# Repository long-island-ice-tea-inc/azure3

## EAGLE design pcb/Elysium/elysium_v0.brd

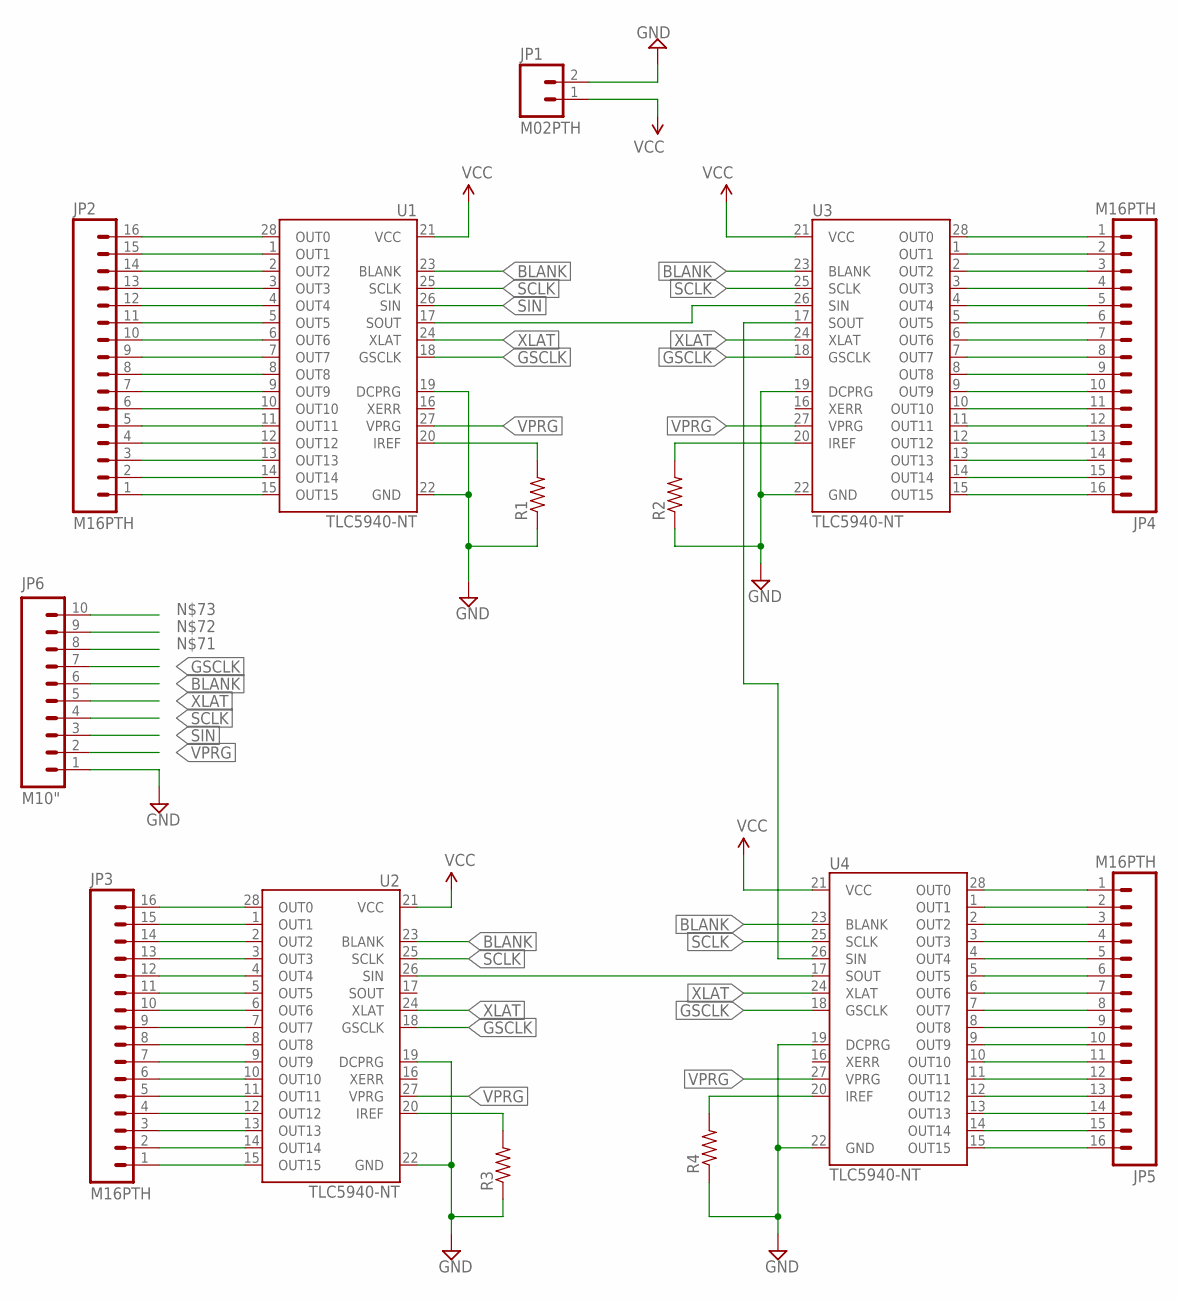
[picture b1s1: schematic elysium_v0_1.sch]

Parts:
JP1: M02PTH; 1X02
JP2, JP3, JP4, JP5: M16PTH; 1X16
JP6: M10"; 1X10
R1, R2, R3, R4: RESISTOREZ; AXIAL-0.3EZ
U1, U2, U3, U4: TLC5940-NT; DIL28-3

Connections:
BLANK: JP6.6, U1.23 (BLANK), U2.23 (BLANK), U3.23 (BLANK), U4.23 (BLANK)
GND: JP1.2, JP6.1, R1.P$1 (1), R2.P$1 (1), R3.P$1 (1), R4.P$1 (1), U1.19 (DCPRG), U1.22 (GND), U2.19 (DCPRG), U2.22 (GND), U3.19 (DCPRG), U3.22 (GND), U4.19 (DCPRG), U4.22 (GND)
GSCLK: JP6.7, U1.18 (GSCLK), U2.18 (GSCLK), U3.18 (GSCLK), U4.18 (GSCLK)
unnamed: JP2.16, U1.28 (OUT0)
unnamed: JP2.15, U1.1 (OUT1)
unnamed: JP2.14, U1.2 (OUT2)
unnamed: JP2.13, U1.3 (OUT3)
unnamed: JP2.12, U1.4 (OUT4)
unnamed: JP2.11, U1.5 (OUT5)
unnamed: JP2.10, U1.6 (OUT6)
unnamed: JP2.9, U1.7 (OUT7)
unnamed: JP2.8, U1.8 (OUT8)
unnamed: JP2.7, U1.9 (OUT9)
unnamed: JP2.6, U1.10 (OUT10)
unnamed: JP2.5, U1.11 (OUT11)
unnamed: JP2.4, U1.12 (OUT12)
unnamed: JP2.3, U1.13 (OUT13)
unnamed: JP2.2, U1.14 (OUT14)
unnamed: JP2.1, U1.15 (OUT15)
unnamed: JP4.1, U3.28 (OUT0)
unnamed: JP4.2, U3.1 (OUT1)
unnamed: JP4.3, U3.2 (OUT2)
unnamed: JP4.4, U3.3 (OUT3)
unnamed: JP4.5, U3.4 (OUT4)
unnamed: JP4.6, U3.5 (OUT5)
unnamed: JP4.7, U3.6 (OUT6)
unnamed: JP4.8, U3.7 (OUT7)
unnamed: JP4.9, U3.8 (OUT8)
unnamed: JP4.10, U3.9 (OUT9)
unnamed: JP4.11, U3.10 (OUT10)
unnamed: JP4.12, U3.11 (OUT11)
unnamed: JP4.13, U3.12 (OUT12)
unnamed: JP4.14, U3.13 (OUT13)
unnamed: JP4.15, U3.14 (OUT14)
unnamed: JP4.16, U3.15 (OUT15)
unnamed: JP3.16, U2.28 (OUT0)
unnamed: JP3.15, U2.1 (OUT1)
unnamed: JP3.14, U2.2 (OUT2)
unnamed: JP3.13, U2.3 (OUT3)
unnamed: JP3.12, U2.4 (OUT4)
unnamed: JP3.11, U2.5 (OUT5)
unnamed: JP3.10, U2.6 (OUT6)
unnamed: JP3.9, U2.7 (OUT7)
unnamed: JP3.8, U2.8 (OUT8)
unnamed: JP3.7, U2.9 (OUT9)
unnamed: JP3.6, U2.10 (OUT10)
unnamed: JP3.5, U2.11 (OUT11)
unnamed: JP3.4, U2.12 (OUT12)
unnamed: JP3.3, U2.13 (OUT13)
unnamed: JP3.2, U2.14 (OUT14)
unnamed: JP3.1, U2.15 (OUT15)
unnamed: JP5.1, U4.28 (OUT0)
unnamed: JP5.2, U4.1 (OUT1)
unnamed: JP5.3, U4.2 (OUT2)
unnamed: JP5.4, U4.3 (OUT3)
unnamed: JP5.5, U4.4 (OUT4)
unnamed: JP5.6, U4.5 (OUT5)
unnamed: JP5.7, U4.6 (OUT6)
unnamed: JP5.8, U4.7 (OUT7)
unnamed: JP5.9, U4.8 (OUT8)
unnamed: JP5.10, U4.9 (OUT9)
unnamed: JP5.11, U4.10 (OUT10)
unnamed: JP5.12, U4.11 (OUT11)
unnamed: JP5.13, U4.12 (OUT12)
unnamed: JP5.14, U4.13 (OUT13)
unnamed: JP5.15, U4.14 (OUT14)
unnamed: JP5.16, U4.15 (OUT15)
unnamed: U1.17 (SOUT), U3.26 (SIN)
unnamed: U3.17 (SOUT), U4.26 (SIN)
unnamed: U2.26 (SIN), U4.17 (SOUT)
unnamed: R1.P$2 (2), U1.20 (IREF)
unnamed: R2.P$2 (2), U3.20 (IREF)
unnamed: R3.P$2 (2), U2.20 (IREF)
unnamed: R4.P$2 (2), U4.20 (IREF)
SCLK: JP6.4, U1.25 (SCLK), U2.25 (SCLK), U3.25 (SCLK), U4.25 (SCLK)
SIN: JP6.3, U1.26 (SIN)
VCC: JP1.1, U1.21 (VCC), U2.21 (VCC), U3.21 (VCC), U4.21 (VCC)
VPRG: JP6.2, U1.27 (VPRG), U2.27 (VPRG), U3.27 (VPRG), U4.27 (VPRG)
XLAT: JP6.5, U1.24 (XLAT), U2.24 (XLAT), U3.24 (XLAT), U4.24 (XLAT)

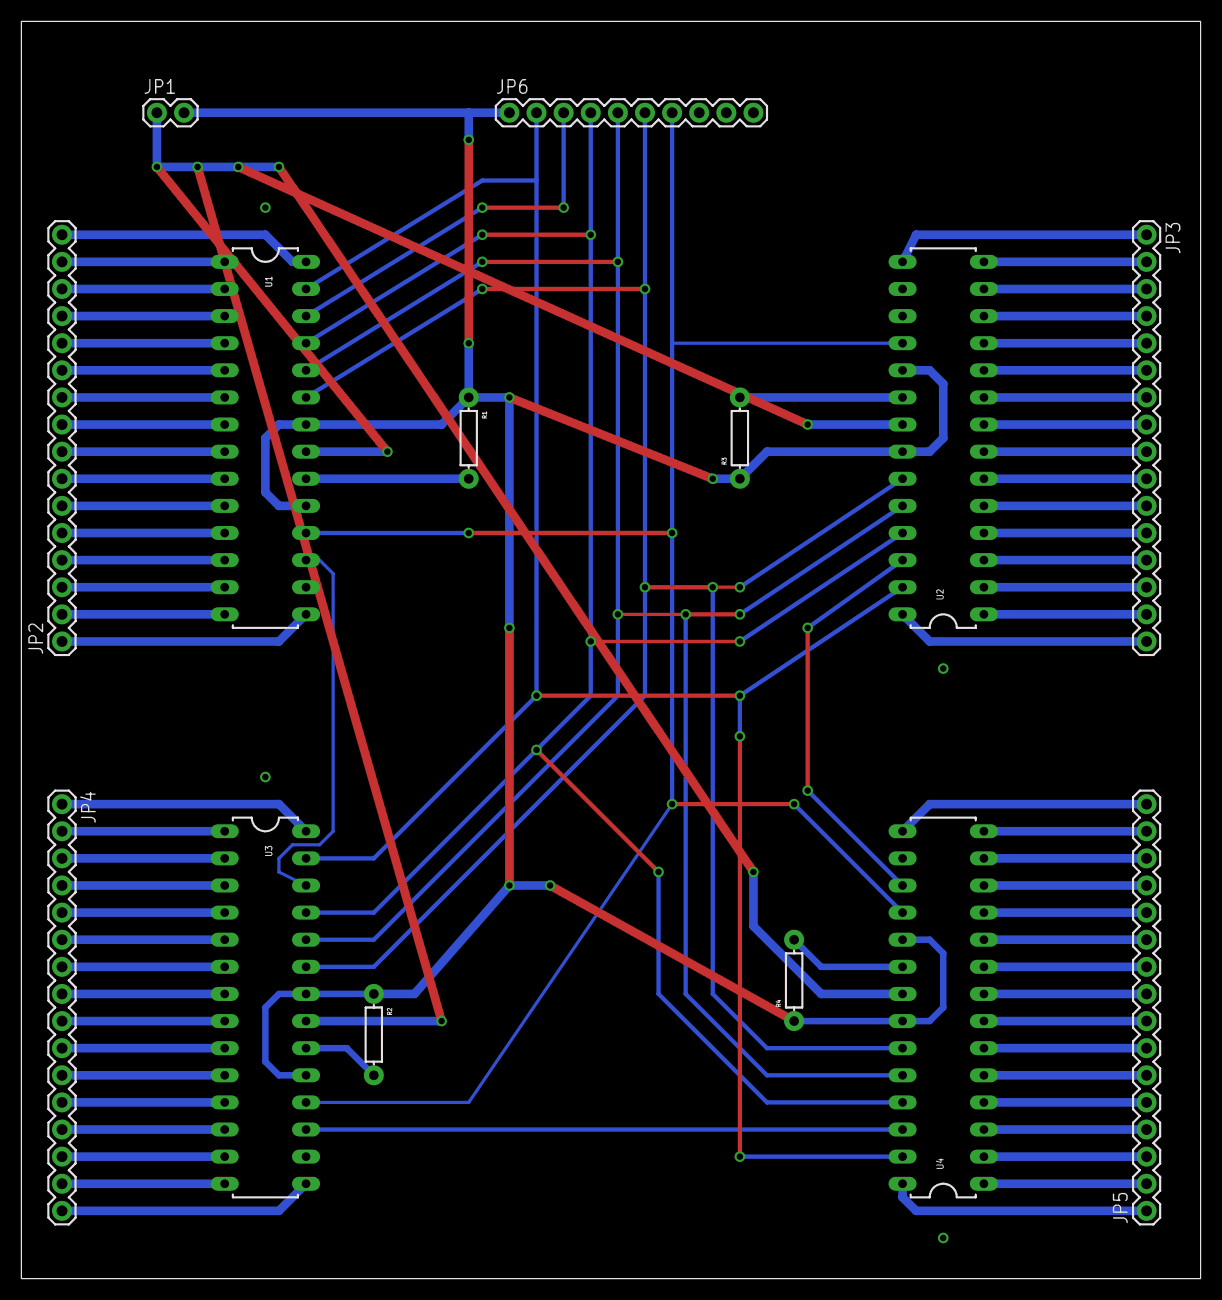
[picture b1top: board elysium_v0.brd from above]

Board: 2 copper layers, 110.5 x 117.8 mm, 14 parts (0 on the bottom side), 79 nets.

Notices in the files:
parts and their libraries:
SparkFun-DigitalIC: Licensing: CC v3.0 Share-Alike You are welcome to use this library for commercial purposes.
